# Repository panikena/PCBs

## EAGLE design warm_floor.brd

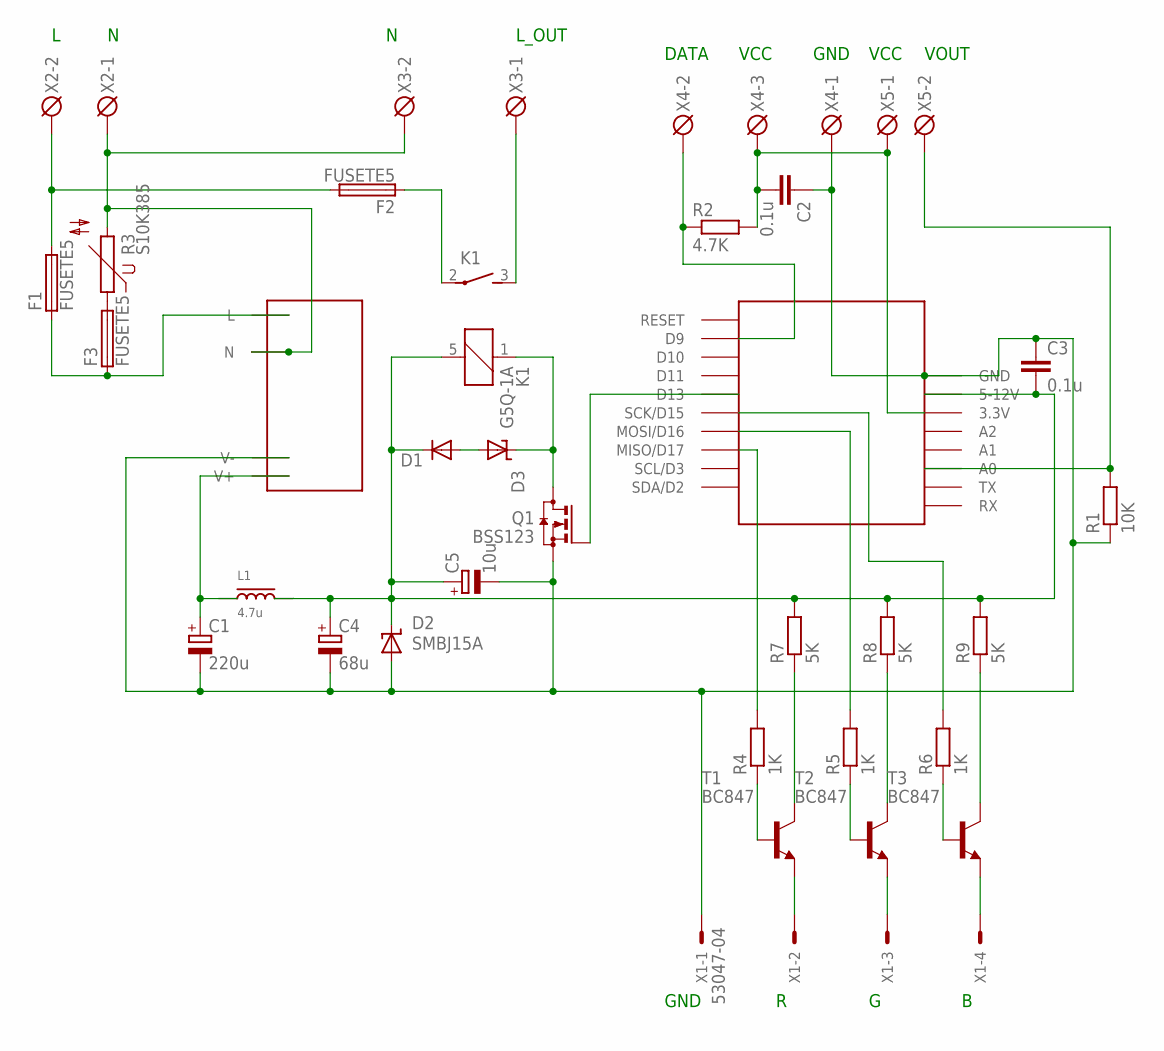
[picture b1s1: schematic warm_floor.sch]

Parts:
C1: 220u; E2,5-6
C2, C3: 0.1u; C0805
C4: 68u; E2,5-7
C5: 10u; E2,5-6
D1: DIODE-SOD123; SOD123
D2: SMBJ15A; SMBJ
D3: SUPPRESSOR-SMBJ; SMBJ
F1, F2, F3: FUSETE5; TE5
K1: G5Q-1A
L1: 4.7u; LQH43
Q1: BSS123; SOT23
R1: 10K; R0805
R2: 4.7K; R0805
R3: S10K385
R4, R5, R6: 1K; R0805
R7, R8, R9: 5K; R0805
T1, T2, T3: BC847; SOT23
U$1: SMARTBRICK
U$2: NA01/02-T2SXX
X1: 53047-04
X2, X3: DG3XX-025.0; DG300-5.0-02P
X4: DG3XX-03-3.5; DG350-3.5-03P
X5: DG3XX-02-3.5; DG350-3.5-02P

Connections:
3.3V: C2.2, R2.2, U$1.3.3V, X4.3, X5.1
DATA: R2.1, U$1.D9, X4.2
GND: C1.-, C2.1, C3.1, C4.-, C5.-, D2.A, Q1.2 (S), R1.1, U$1.GND, U$2.V-, X1.1, X4.1
L: F1.2, F2.2, X2.2
N: R3.2, U$2.N, X2.1, X3.2
unnamed: C1.+, L1.P$1, U$2.V+
unnamed: F3.2, R3.1
unnamed: D3.C, K1.1, Q1.3 (D)
unnamed: F2.1, K1.2
unnamed: K1.3 (S), X3.1
unnamed: D1.A, D3.A
unnamed: T1.2 (E), X1.2
unnamed: R5.2, U$1.MOSI/D16
unnamed: T2.2 (E), X1.3
unnamed: T3.2 (E), X1.4
unnamed: R4.1, T1.1 (B)
unnamed: R5.1, T2.1 (B)
unnamed: R6.1, T3.1 (B)
unnamed: R4.2, U$1.MISO/D17
unnamed: R6.2, U$1.SCK/D15
unnamed: R9.1, T3.3 (C)
unnamed: R8.1, T2.3 (C)
unnamed: R7.1, T1.3 (C)
NTC: R1.2, U$1.A0, X5.2
PS_L: F1.1, F3.1, U$2.L
RELAY: Q1.1 (G), U$1.D13
VCC: C3.2, C4.+, C5.+, D1.C, D2.C, K1.5 (2), L1.P$2, R7.2, R8.2, R9.2, U$1.VIN (5-12V)

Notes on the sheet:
GND
DATA
VCC
VOUT
L_OUT

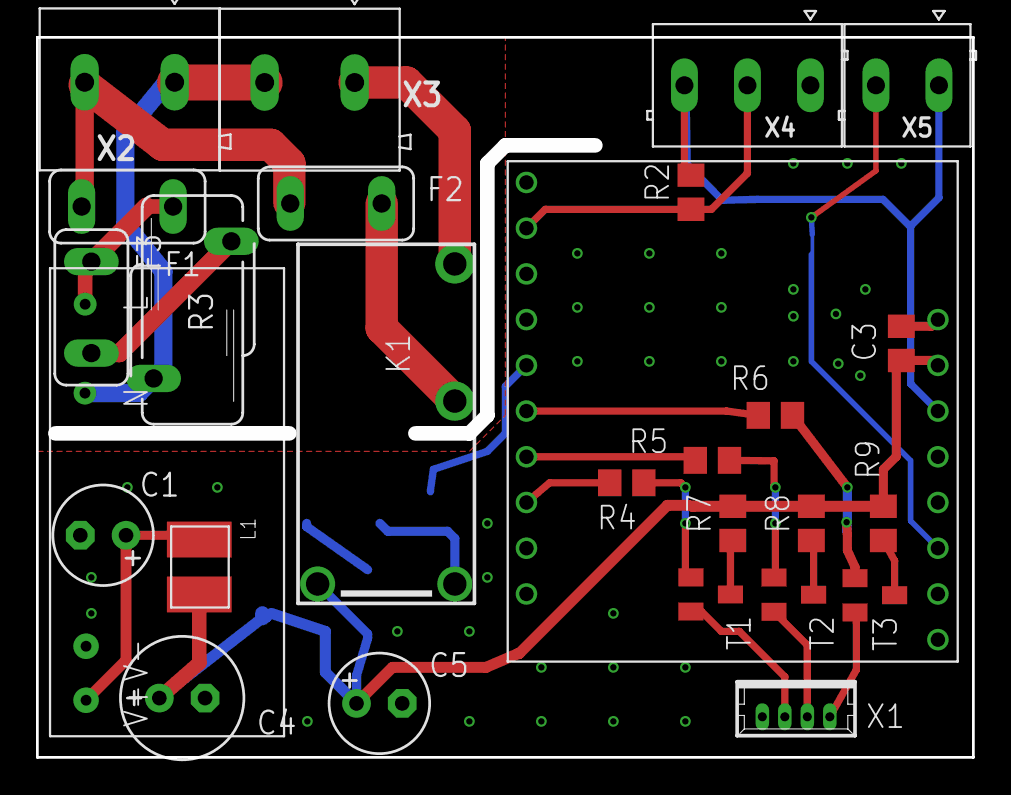
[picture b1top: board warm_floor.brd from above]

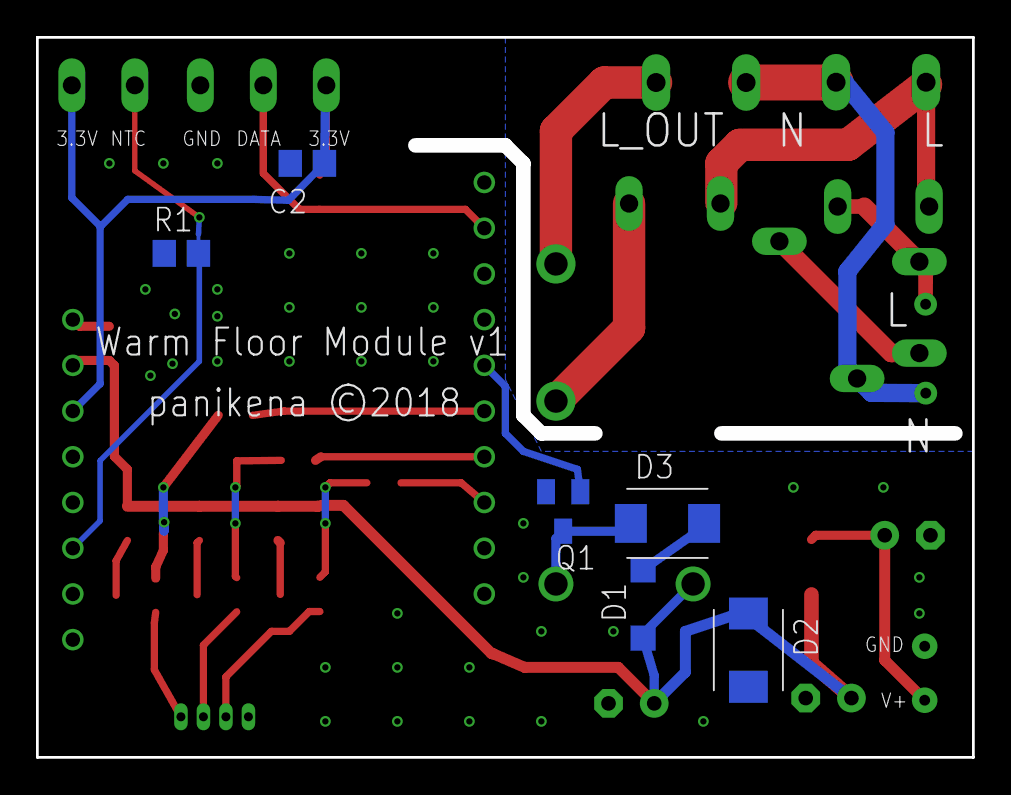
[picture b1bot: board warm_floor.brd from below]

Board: 2 copper layers, 51.3 x 39.3 mm, 33 parts (6 on the bottom side), 27 nets.

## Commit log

2018-05-02 linked all wires
2018-07-02 Last G2R version
2018-07-19 Pre-publish commit
2019-01-04 Added custom KiCad lib

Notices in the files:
warm_floor.brd:
panikena ©2018
